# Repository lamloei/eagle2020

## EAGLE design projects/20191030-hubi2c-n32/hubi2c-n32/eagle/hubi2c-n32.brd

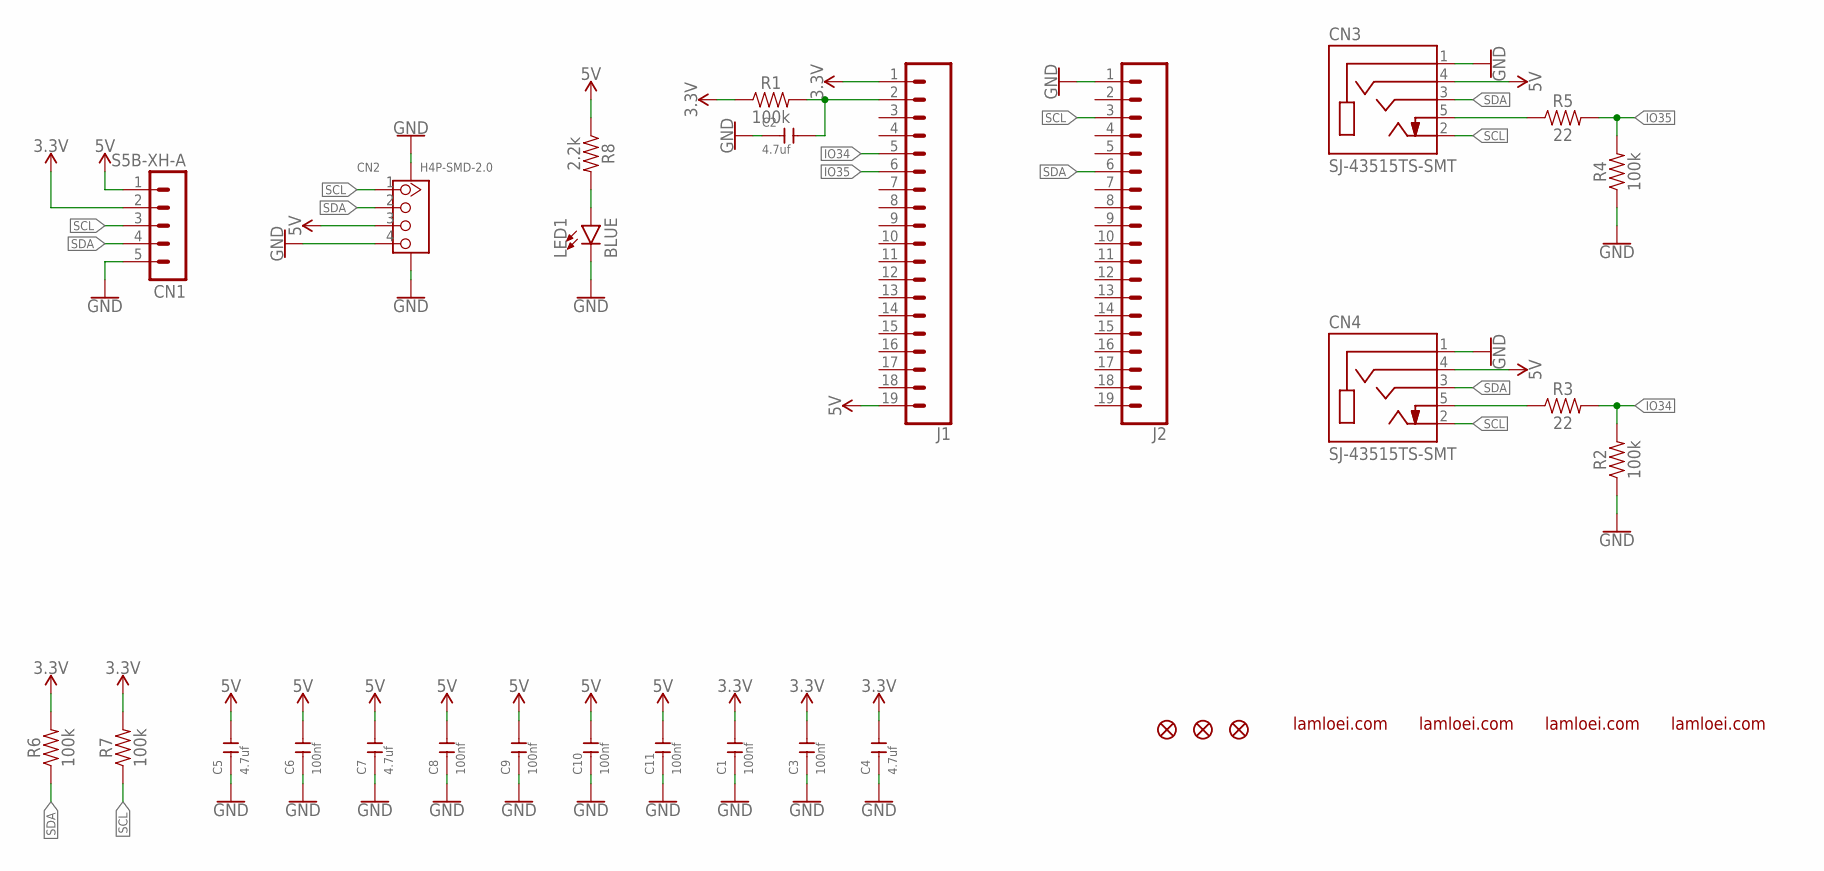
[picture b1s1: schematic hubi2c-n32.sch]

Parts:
C1, C3, C6, C8, C9, C10, C11: 100nf; C0402
C2, C4, C5, C7: 4.7uf; C0603
CN1: S5B-XH-A
CN2: H4P-SMD-2.0; HW4-SMD-2.0
CN3, CN4: SJ-43515TS-SMT; CUI_SJ-43515TS-SMT
J1, J2: CONN_19; 1X19
LED1: BLUE; LED-0603
R1, R2, R4, R6, R7: 100k; 0603
R3, R5: 22; 0603
R8: 2.2k; 0603
ZFD1, ZFD2, ZFD3: FIDUCIAL1X2; FIDUCIAL-1X2
ZL1, ZL2, ZL3: LAMLEOI_LOGO_3
ZL4: LAMLOEI_BIGLOGO

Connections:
3.3V: C1.2, C3.2, C4.2, CN1.2, J1.1, R1.1, R6.2, R7.2
5V: C5.2, C6.2, C7.2, C8.2, C9.2, C10.2, C11.2, CN1.1, CN2.3, CN3.4 (RING2), CN4.4 (RING2), J1.19, R8.1
GND: C1.1, C2.1, C3.1, C4.1, C5.1, C6.1, C7.1, C8.1, C9.1, C10.1, C11.1, CN1.5, CN2.4, CN2.SS1, CN2.SS2, CN3.1 (SLEEVE), CN4.1 (SLEEVE), J2.1, LED1.C, R2.1, R4.1
IO34: J1.5, R2.2, R3.2
IO35: J1.6, R4.2, R5.2
unnamed: CN4.5 (TIP_SWITCH), R3.1
unnamed: CN3.5 (TIP_SWITCH), R5.1
unnamed: C2.2, J1.2, R1.2
unnamed: LED1.A, R8.2
SCL: CN1.3, CN2.1, CN3.2 (TIP), CN4.2 (TIP), J2.3, R7.1
SDA: CN1.4, CN2.2, CN3.3 (RING1), CN4.3 (RING1), J2.6, R6.1

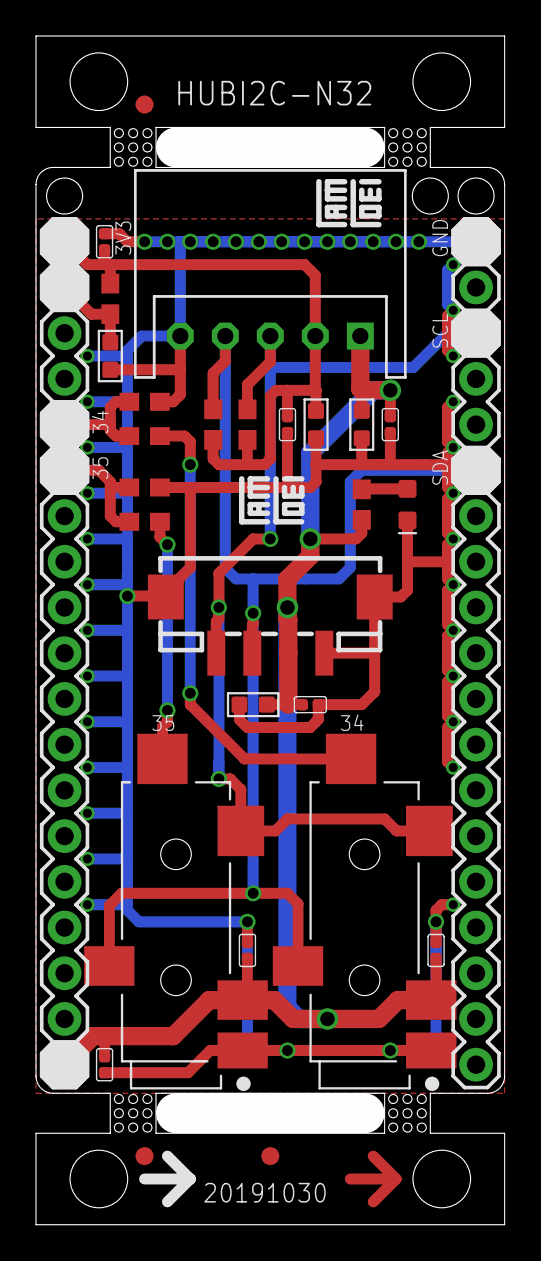
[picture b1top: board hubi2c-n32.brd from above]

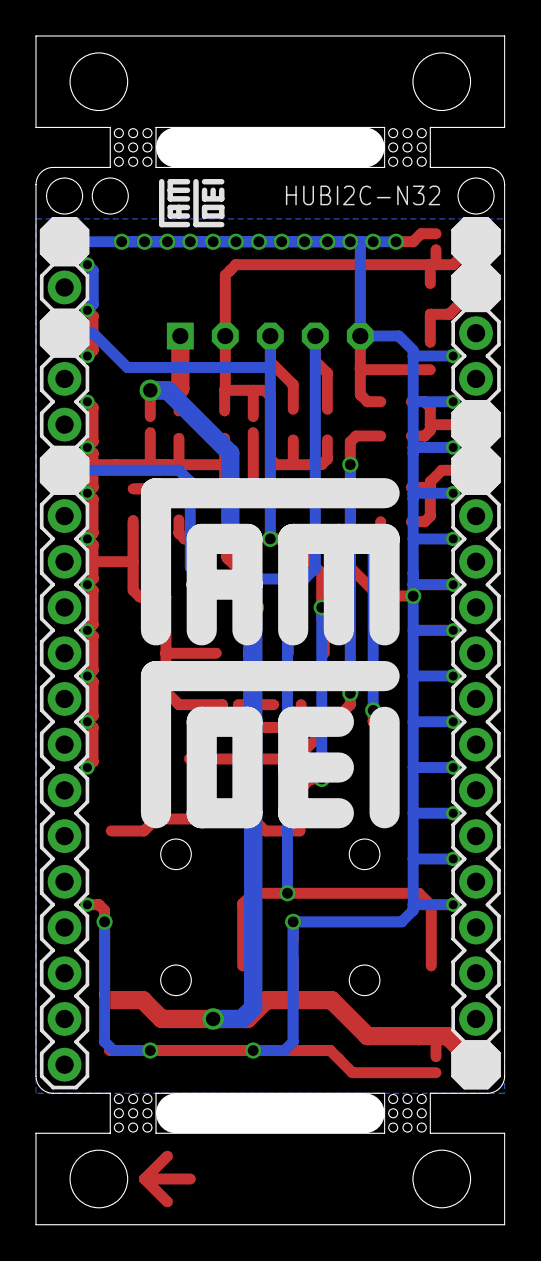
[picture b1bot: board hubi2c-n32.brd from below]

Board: 2 copper layers, 26.0 x 66.0 mm, 33 parts (2 on the bottom side), 11 nets.

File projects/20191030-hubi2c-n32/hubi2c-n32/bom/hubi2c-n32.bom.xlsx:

|  | HUBI2C N32 |  | v1 | 43768
Item | Quantity | Reference | Part | Footprint | Mfg | Mfg P/N | Vendor | Vendor P/N | Notes
1 | 7 | C1, C3, C6, C8, C9, C10, C11 | 100nF 50V 0402 Multilayer Ceramic Capacitors | 0402 | Murata | GRM155R71H104KE14D | LCSC | C77020
2 | 4 | C2, C4, C5, C7 | 4.7uF 16V 0603 Multilayer Ceramic Capacitors | 0603 | Murata | GRM188Z71C475KE21D | LCSC | C389010
3 | 1 | CN1 | WAFER Connector 5 Pins,Pitch 2.50mm,Right Angle | 4P-2.50MM | GTK | 100105RT/RH | ES | 0007-0742-6
4 | 1 | CN2 | SMD,P=2mm Wire To Board | 4S-2.00MM | Boom | C161188 | LCSC | C161188
5 | 2 | CN3,CN4 | 3.5mm Audio Jacks,Tip Switch | 5-SMD | CUI | SJ-43515TS-SMT-TR | ES | 0559-0007-3
6 | 2 | J1, J2 | PIN HEADER | 19P-2.54MM |  |  |  |  | NOT INSTALL
7 | 1 | LED1 | LIGHT EMITTING DIODES (LED) BLUE | 0603 | Everlight | 19-217/BHC-ZL1M2RY/3T | LCSC | C72041
8 | 5 | R1, R2, R4, R6, R7 | 100K ±1% 1/10W 0603 Chip Resistor | 0603 | YAGEO | RC0603FR-07100KL | LCSC | C14675
9 | 2 | R3, R5 | 22 ±1% 1/10W 0603 Chip Resistor | 0603 | YAGEO | RC0603FR-0722RL | LCSC | C107701
10 | 1 | R8 | 2.2K ±1% 1/10W 0603 Chip Resistor | 0603 | YAGEO | RC0603FR-072K2L | LCSC | C114662

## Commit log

2019-11-18 :lollipop: Added .gitattributes & .gitignore files

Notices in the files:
parts and their libraries:
SparkFun-Connectors-3: Licensing: Creative Commons ShareAlike 4.0 International - https://creativecommons.org/licenses/by-sa/4.0
